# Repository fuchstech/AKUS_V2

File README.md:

# Bu repo Akıllı Ulaşım Sistemleri Yarışması için hazırlanmış olup Teknofest 2023 Fikir Maratonun'da Üçüncü olmuş AKUS projemizi baz alarak geliştirilmiştir. 
Derece alan projenin sunumu için https://github.com/fuchstech/AKUS linkini ziyaret edebilirsiniz

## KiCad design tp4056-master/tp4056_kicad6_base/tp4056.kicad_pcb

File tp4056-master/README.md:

# tp4056
TP4056 charger kicad schematics

Kicad version with tp4056 footprint and schematics

TP4056 battery charging module with protection.  KICAD v6. old version for KICAD v5.

Charging current set to 130ma (R=10kOm)

tp4056 for DIY hand soldering with microUSB.

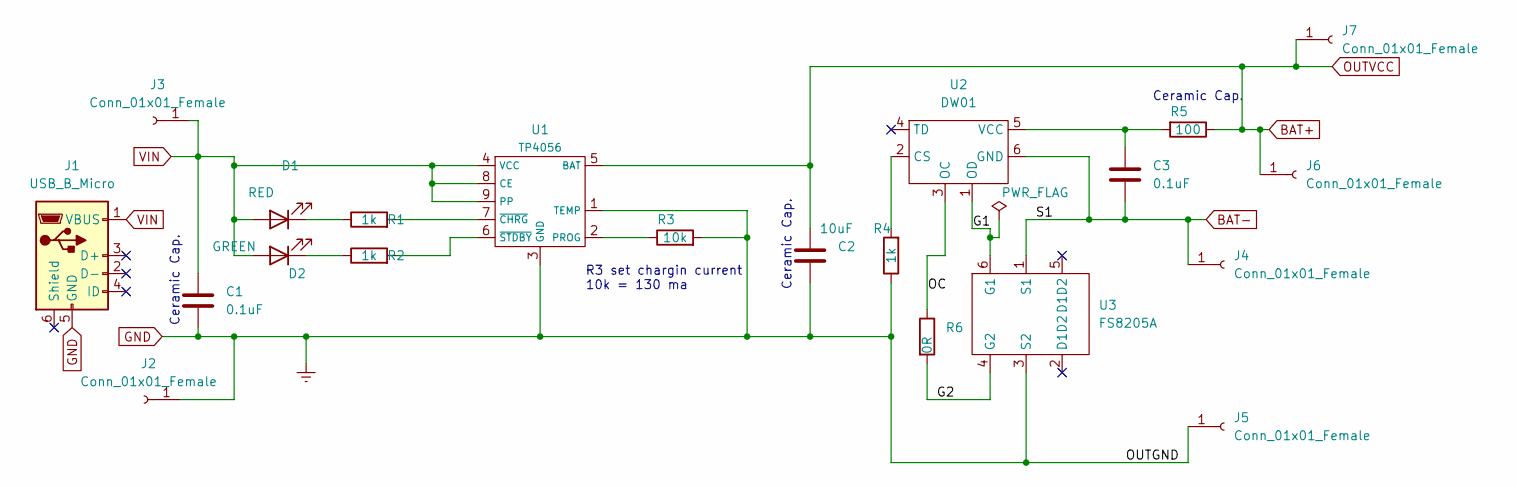
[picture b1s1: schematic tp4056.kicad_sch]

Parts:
C1, C3: 0.1uF; C_0805_2012Metric_Pad1.18x1.45mm_HandSolder
C2: 10uF; C_0805_2012Metric_Pad1.18x1.45mm_HandSolder
D1: RED; LED_0805_2012Metric_Pad1.15x1.40mm_HandSolder
D2: GREEN; LED_0805_2012Metric_Pad1.15x1.40mm_HandSolder
J1: USB_B_Micro; tp4056_USB_Micro-B_Molex_47346-0001_fix
J2, J3, J4, J5, J6, J7: Conn_01x01_Female; PinSocket_1x01_P2.54mm_Vertical
R1, R2, R4: 1k; R_0603_1608Metric_Pad0.98x0.95mm_HandSolder
R3: 10k; R_0805_2012Metric_Pad1.20x1.40mm_HandSolder
R5: 100; R_0805_2012Metric_Pad1.20x1.40mm_HandSolder
R6: 0R; R_1206_3216Metric_Pad1.30x1.75mm_HandSolder
U1: TP4056; SOIC-8-1EP_3.9x4.9mm_P1.27mm_EP2.29x3mm
U2: DW01; SOT-23-6_Handsoldering
U3: FS8205A; SOT-23-6_Handsoldering

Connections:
/G1: U2.1 (OD), U3.6 (G1)
/G2: R6.2, U3.4 (G2)
/OC: R6.1, U2.3 (OC)
BAT+: C2.1, J6.1, J7.1, R5.1, U1.5 (BAT)
BAT-: C3.2, J4.1, U2.6 (GND), U3.1 (S1)
GND: C1.2, C2.2, J1.5 (GND), J2.1, J5.1, R3.2, R4.1, U1.1 (TEMP), U1.3 (GND), U3.3 (S2)
unnamed: C3.1, R5.2, U2.5 (VCC)
unnamed: D1.1 (K), R1.1
unnamed: D2.1 (K), R2.1
unnamed: R1.2, U1.7 (~CHRG)
unnamed: R2.2, U1.6 (~STDBY)
unnamed: R3.1, U1.2 (PROG)
unnamed: R4.2, U2.2 (CS)
VIN: C1.1, D1.2 (A), D2.2 (A), J1.1 (VBUS), J3.1, U1.4 (VCC), U1.8 (CE), U1.9 (PP)

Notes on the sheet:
Ceramic Cap.
R3 set chargin current 10k = 130 ma

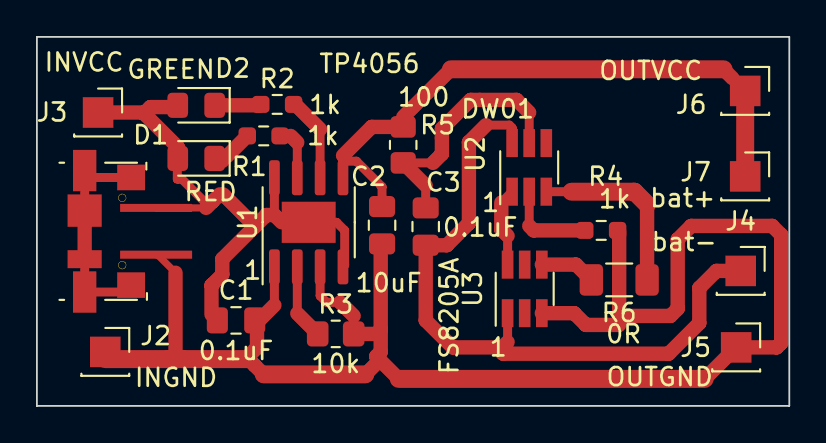
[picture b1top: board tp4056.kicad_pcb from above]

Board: 2 copper layers, 41.8 x 20.5 mm, 21 parts (0 on the bottom side), 14 nets.

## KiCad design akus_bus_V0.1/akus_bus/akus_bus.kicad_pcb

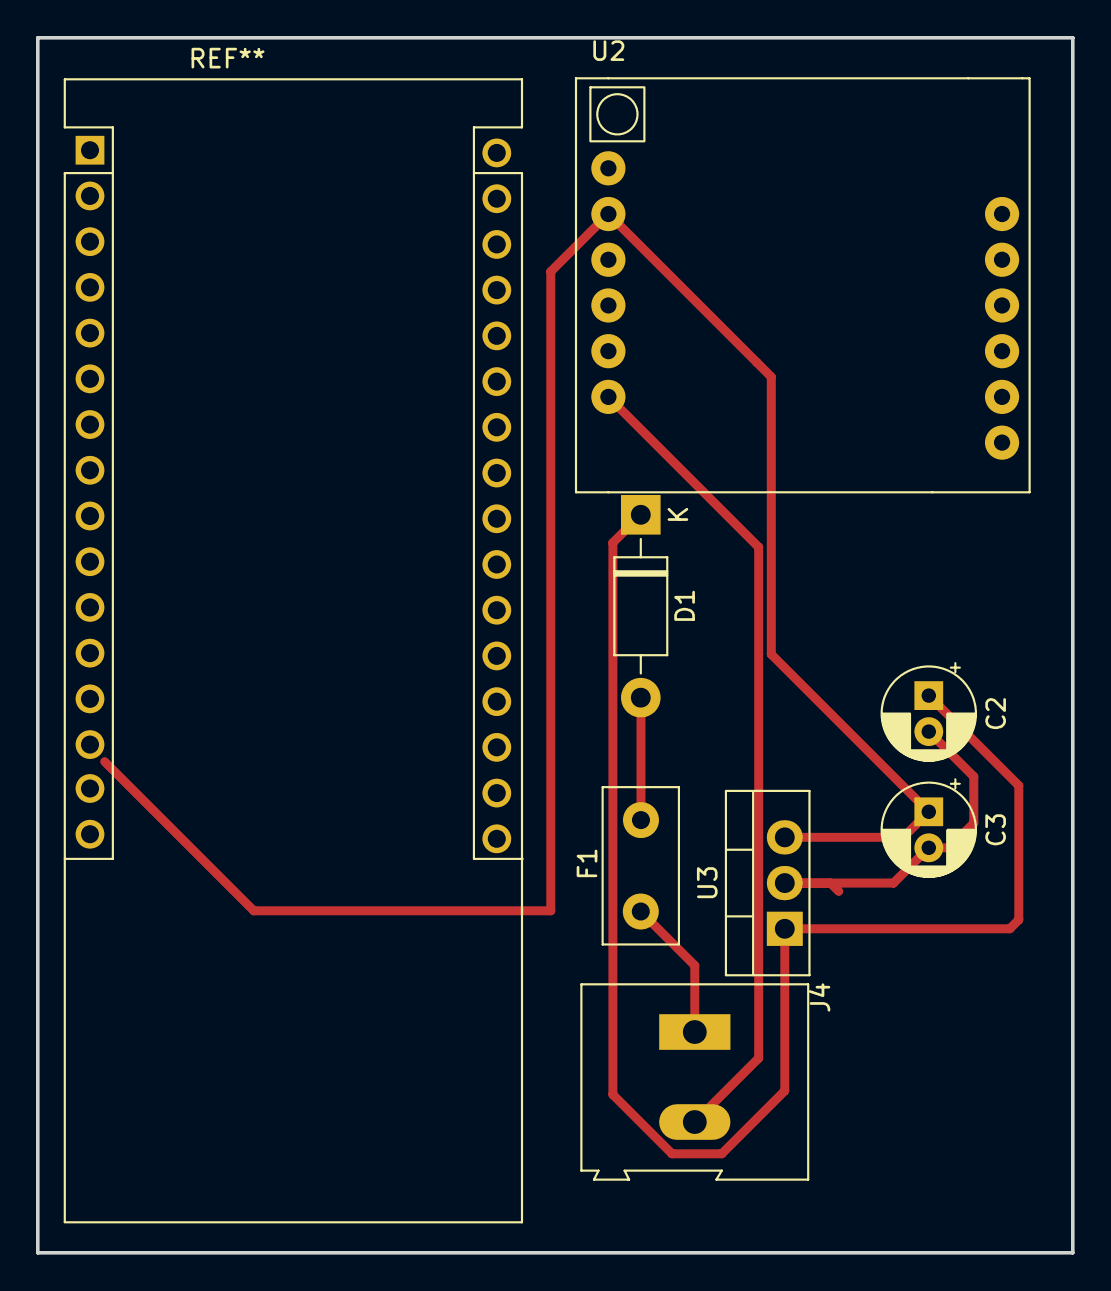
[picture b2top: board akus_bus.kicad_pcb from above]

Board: 2 copper layers, 57.5 x 67.5 mm, 7 parts (0 on the bottom side), 5 nets.

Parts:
C2: 10uF; CP_Radial_D5.0mm_P2.00mm
C3: 1uF; CP_Radial_D5.0mm_P2.00mm
D1: 1N4007; D_DO-41_SOD81_P10.16mm_Horizontal
F1: sigorta 2A; Fuse_Littelfuse_395Series
J4: 12V; TerminalBlock_Altech_AK300-2_P5.00mm
U2: SIM800L-CORE
U3: LM7805_TO220; TO-220-3_Vertical

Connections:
unnamed: D1.2 (A), F1.2
unnamed: C2.1, D1.1 (K), U3.1 (VI)
unnamed: F1.1, J4.1
unnamed: C2.2, C3.2, J4.2, U2.6 (GND), U3.2 (GND)
unnamed: C3.1, U2.2 (VCC), U3.3 (VO)

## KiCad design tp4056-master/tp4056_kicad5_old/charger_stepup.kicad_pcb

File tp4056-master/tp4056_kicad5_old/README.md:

# tp4056
TP4056 charger kicad schematics

for Kicad 5 version 

TP4056 Lithium Cell Charger Module with Battery Protection  without usb connector

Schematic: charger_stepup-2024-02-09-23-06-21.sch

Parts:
C1, C2: 0.1uF; C_0805_HandSoldering
C3: 10uF; C_0805_HandSoldering
D1, D2: LED; LED_0603_HandSoldering
J1: CONN_in-; Pin_Header_Straight_1x01_Pitch2.54mm
J2: CONN_in+; Pin_Header_Straight_1x01_Pitch2.54mm
J3: conOut+; Pin_Header_Straight_1x01_Pitch2.54mm
J4: conOut-; Pin_Header_Straight_1x01_Pitch2.54mm
J5: CONN_bat+; Pin_Header_Straight_1x01_Pitch2.54mm
J6: CONN_bat-; Pin_Header_Straight_1x01_Pitch2.54mm
R1, R2, R4: 1k; R_0603_HandSoldering
R3: 10k; R_0603_HandSoldering
R5: 100; R_0603_HandSoldering
U1: TP4056; TP4056_SOP-8-PP
U2: DW01; SOT-23-6_Handsoldering
U3: FS8205A; TSSOP-8_4.4x3mm_Pitch0.65mm

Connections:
BAT+: C3.1, J3.1, J5.1, R5.1, U1.5
BAT-: C2.2, J6.1, U2.6, U3.2, U3.3
IN+: C1.1, D1.2 (A), D2.2 (A), J2.1, U1.4, U1.8, U1.9
IN-: C1.2, C3.2, J1.1, J4.1, R3.1, R4.1, U1.1, U1.3, U3.6, U3.7
unnamed: C2.1, R5.2, U2.5
unnamed: D1.1 (K), R2.2
unnamed: D2.1 (K), R1.2
unnamed: R1.1, U1.6
unnamed: R2.1, U1.7
unnamed: R3.2, U1.2
unnamed: R4.2, U2.2
unnamed: U2.1, U3.4
unnamed: U2.3, U3.5

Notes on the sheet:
Set Charging Current to 130ma
ceramic cap

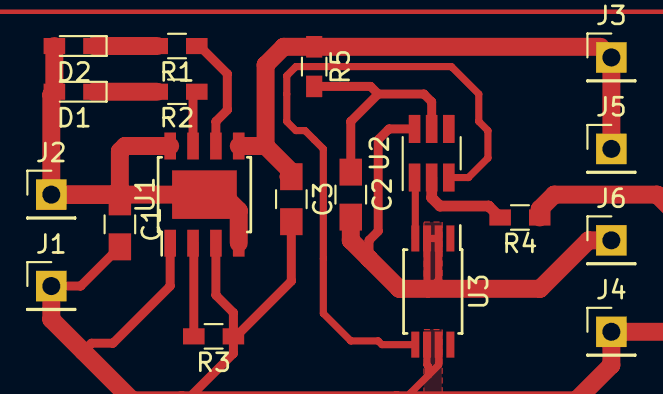
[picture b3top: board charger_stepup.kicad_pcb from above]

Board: 2 copper layers, 19 parts (0 on the bottom side), 13 nets.

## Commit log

2024-02-09 libraries update
2024-02-10 update bus
